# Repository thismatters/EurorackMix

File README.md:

# Mix

Audio signal mixing. Basic module with simple OP Amp design.

The KiCAD project here uses the library/footprints [found in my companion repo](https://github.com/thismatters/EurorackKiCAD).

## Size

30hp on a 1u rack.

## Inputs

4x patch inputs and 4x potentiometers for adjusting the apparent effect of a patch input

## Outputs

Single 1/4" phone jack output.
4 LED array indicating output level.

## Notes

LED array takes some cues from the [MFOS Multifunction Module](https://musicfromouterspace.com/analogsynth_new/MULTIFUNCTIONMODULE/pdf/mfm_schempg1_schem.pdf)

## Vendors

There are part numbers in the [BOM](mix.csv) for many of the parts (not for basic passives though) at the following vendors:

* [Mouser](https://www.mouser.com): Needs no introduction. Get your ICs from here (or [digikey](https://www.digikey.com)).
* [Tayda Electronics](https://www.taydaelectronics.com/): Good supplier for passive components; audio jacks, and potentiometers. Their audio jacks are slightly smaller than the thonkiconn from thonk.
* [Love My Switches](https://lovemyswitches.com/): Has [really good knobs](https://lovemyswitches.com/anodized-aluminum-knob-the-lo-fi-1-4-smooth-shaft-12-5mm-od/) to go on those potentiometers!
* [OSHPark](https://oshpark.com/): Fast and (relatively) cheap PCB manufacturer. The [V0 circuit](https://oshpark.com/shared_projects/xlEAsl8K) works pretty well as a mix, but the output level indicator doesn't quite work right, there will be another version.

## Changelog

### V1
- [x] Adds full bridge rectifier to output level indicator
- [x] Adds capacitor and resistor to output level indicator
- [x] Removes capacitor from output op amp
- [x] Updates design langage

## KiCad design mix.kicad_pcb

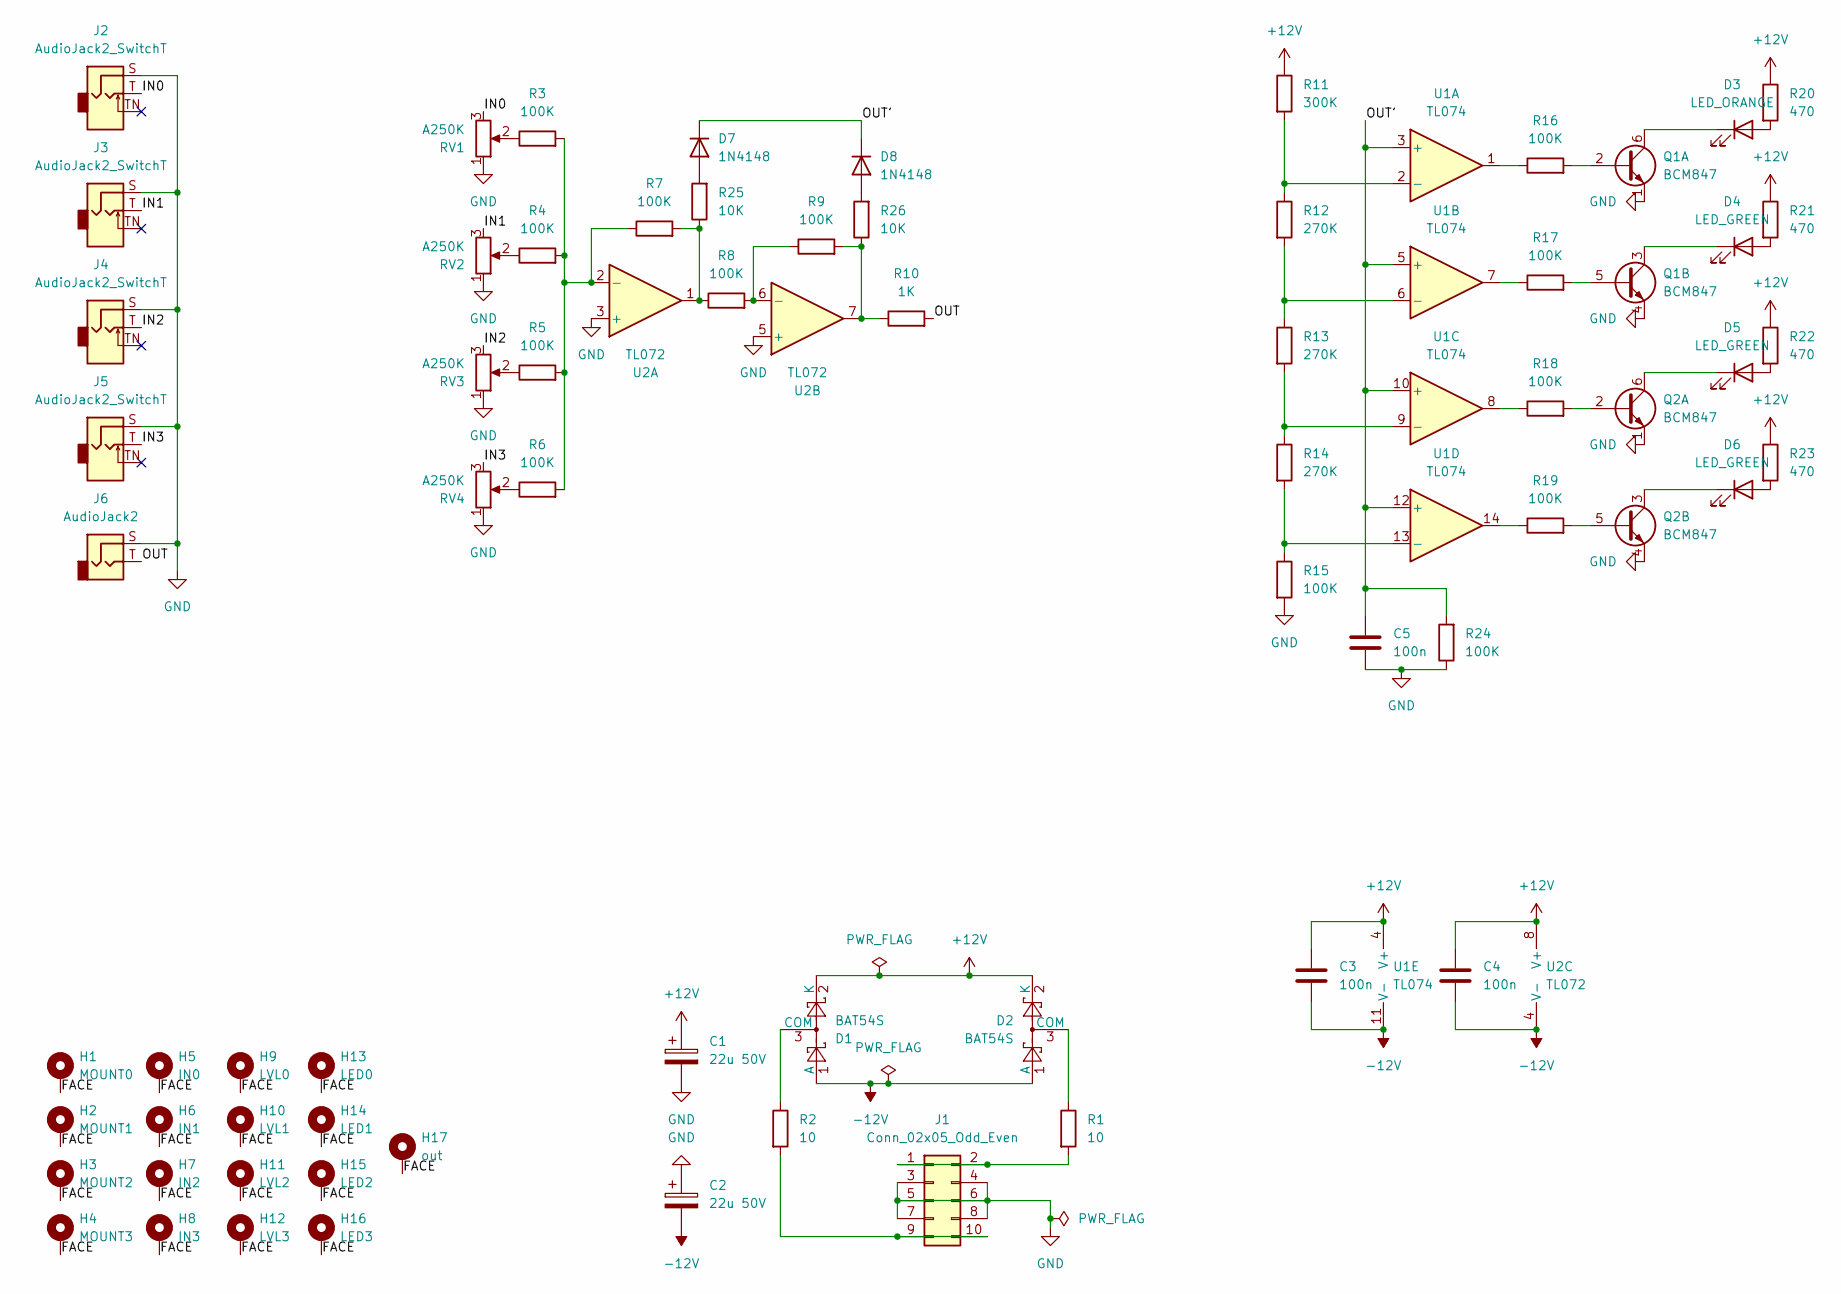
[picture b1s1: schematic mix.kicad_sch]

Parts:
C1, C2: 22u 50V; CP_Radial_D5.0mm_P2.50mm
C3, C4, C5: 100n; C_0805_2012Metric
D1, D2: BAT54S; SOT-23; PartNum 863-BAT54SLT1G
D3: LED_ORANGE; LED_D3.0mm
D4, D5, D6: LED_GREEN; LED_D3.0mm
D7, D8: 1N4148; D_SOD-323_HandSoldering
H1: MOUNT0; Mech-MountingHole
H2: MOUNT1; Mech-MountingHole
H3: MOUNT2; Mech-MountingHole
H4: MOUNT3; Mech-MountingHole
H5: IN0; Mech-AudioJack-Hole-Input
H6: IN1; Mech-AudioJack-Hole-Input
H7: IN2; Mech-AudioJack-Hole-Input
H8: IN3; Mech-AudioJack-Hole-Input
H9: LVL0; Mech-Potentiometer-Hole_level_90deg
H10: LVL1; Mech-Potentiometer-Hole_level_90deg
H11: LVL2; Mech-Potentiometer-Hole_level_90deg
H12: LVL3; Mech-Potentiometer-Hole_level_90deg
H13: LED0; Mech-LED-Hole-3mm-Bezel
H14: LED1; Mech-LED-Hole-3mm-Bezel
H15: LED2; Mech-LED-Hole-3mm-Bezel
H16: LED3; Mech-LED-Hole-3mm-Bezel
H17: out; Mech-Hole-10mm; PartNum 595-TL072CDR
J1: Conn_02x05_Odd_Even; PinHeader_2x05_P2.54mm_Vertical; PartNum A-2939
J2, J3, J4, J5: AudioJack2_SwitchT; AudioJack2_Tayda_A-2566; PartNum A-2566
J6: AudioJack2; AudioJack2_Tayda_A-1009; PartNum A-1009
Q1, Q2: BCM847; TSOP-6_1.65x3.05mm_P0.95mm; PartNum 771-BCM847DS135
R1, R2: 10; R_0805_2012Metric
R3, R4, R5, R6, R7, R8, R9, R15, R16, R17, R18, R19, R24: 100K; R_0805_2012Metric
R10: 1K; R_0805_2012Metric
R11: 300K; R_0805_2012Metric
R12, R13, R14: 270K; R_0805_2012Metric
R20, R21, R22, R23: 470; R_0805_2012Metric
R25, R26: 10K; R_0805_2012Metric
RV1, RV2, RV3, RV4: A250K; Potentiometer_RV16AF-41-15R1
U1: TL074; SOIC-14_3.9x8.7mm_P1.27mm; PartNum 595-TL074CDR
U2: TL072; SOIC-8_3.9x4.9mm_P1.27mm; PartNum 595-TL072CDR

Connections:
+12V: C1.1, C3.1, C4.1, D1.2 (K), D2.2 (K), R11.1, R20.1, R21.1, R22.1, R23.1, U1.4 (V+), U2.8 (V+)
-12V: C2.2, C3.2, C4.2, D1.1 (A), D2.1 (A), U1.11 (V-), U2.4 (V-)
/FACE: H1.1, H2.1, H3.1, H4.1, H5.1, H6.1, H7.1, H8.1, H9.1, H10.1, H11.1, H12.1, H13.1, H14.1, H15.1, H16.1, H17.1
/IN0: J2.T, RV1.3
/IN1: J3.T, RV2.3
/IN2: J4.T, RV3.3
/IN3: J5.T, RV4.3
/OUT: J6.T, R10.2
/OUT': C5.1, D7.1 (K), D8.1 (K), R24.2, U1.3 (+), U1.5 (+), U1.10 (+), U1.12 (+)
GND: C1.2, C2.1, C5.2, J1.3, J1.4, J1.5, J1.6, J1.7, J1.8, J2.S, J3.S, J4.S, J5.S, J6.S, Q1.1 (E1), Q1.4 (E2), Q2.1 (E1), Q2.4 (E2), R15.2, R24.1, RV1.1, RV2.1, RV3.1, RV4.1, U2.3 (+), U2.5 (+)
unnamed: D1.3 (COM), R2.1
unnamed: D2.3 (COM), R1.1
unnamed: D3.2 (A), R20.2
unnamed: D3.1 (K), Q1.6 (C1)
unnamed: D4.2 (A), R21.2
unnamed: D4.1 (K), Q1.3 (C2)
unnamed: D5.2 (A), R22.2
unnamed: D5.1 (K), Q2.6 (C1)
unnamed: D6.2 (A), R23.2
unnamed: D6.1 (K), Q2.3 (C2)
unnamed: D7.2 (A), R25.2
unnamed: D8.2 (A), R26.2
unnamed: J1.1, J1.2, R1.2
unnamed: J1.9, J1.10, R2.2
unnamed: Q1.2 (B1), R16.2
unnamed: Q1.5 (B2), R17.2
unnamed: Q2.2 (B1), R18.2
unnamed: Q2.5 (B2), R19.2
unnamed: R3.1, RV1.2
unnamed: R4.1, RV2.2
unnamed: R5.1, RV3.2
unnamed: R6.1, RV4.2
unnamed: R9.2, R10.1, R26.1, U2.7
unnamed: R16.1, U1.1
unnamed: R17.1, U1.7
unnamed: R18.1, U1.8
unnamed: R19.1, U1.14
unnamed: R7.2, R8.1, R25.1, U2.1
unnamed: R11.2, R12.1, U1.2 (-)
unnamed: R12.2, R13.1, U1.6 (-)
unnamed: R13.2, R14.1, U1.9 (-)
unnamed: R14.2, R15.1, U1.13 (-)
unnamed: R3.2, R4.2, R5.2, R6.2, R7.1, U2.2 (-)
unnamed: R8.2, R9.1, U2.6 (-)

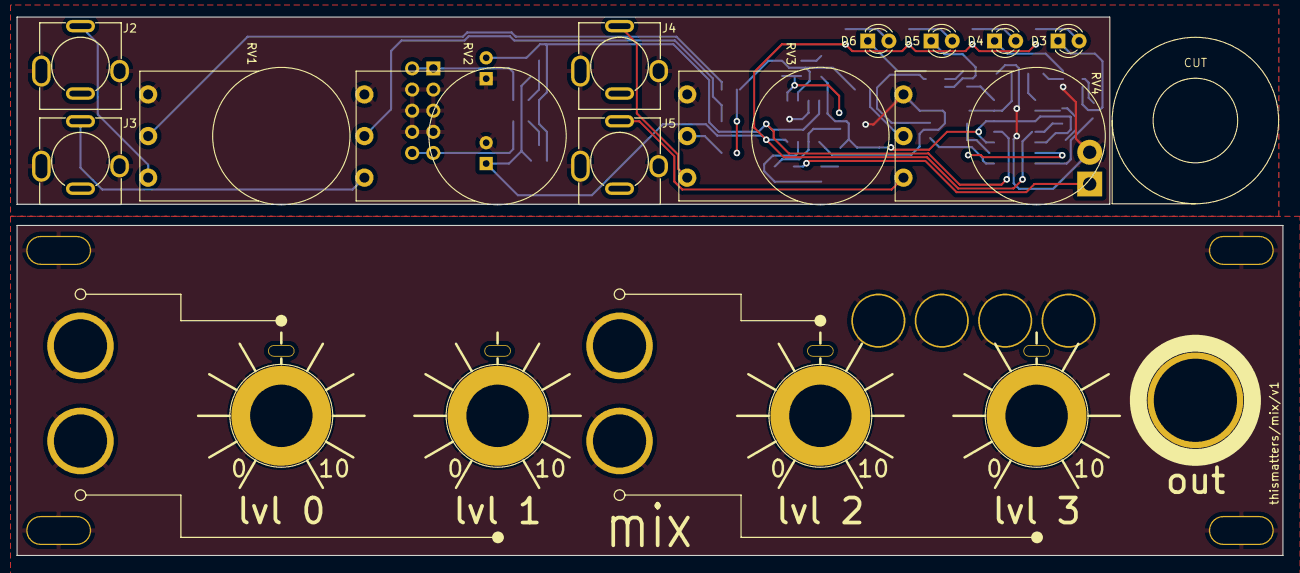
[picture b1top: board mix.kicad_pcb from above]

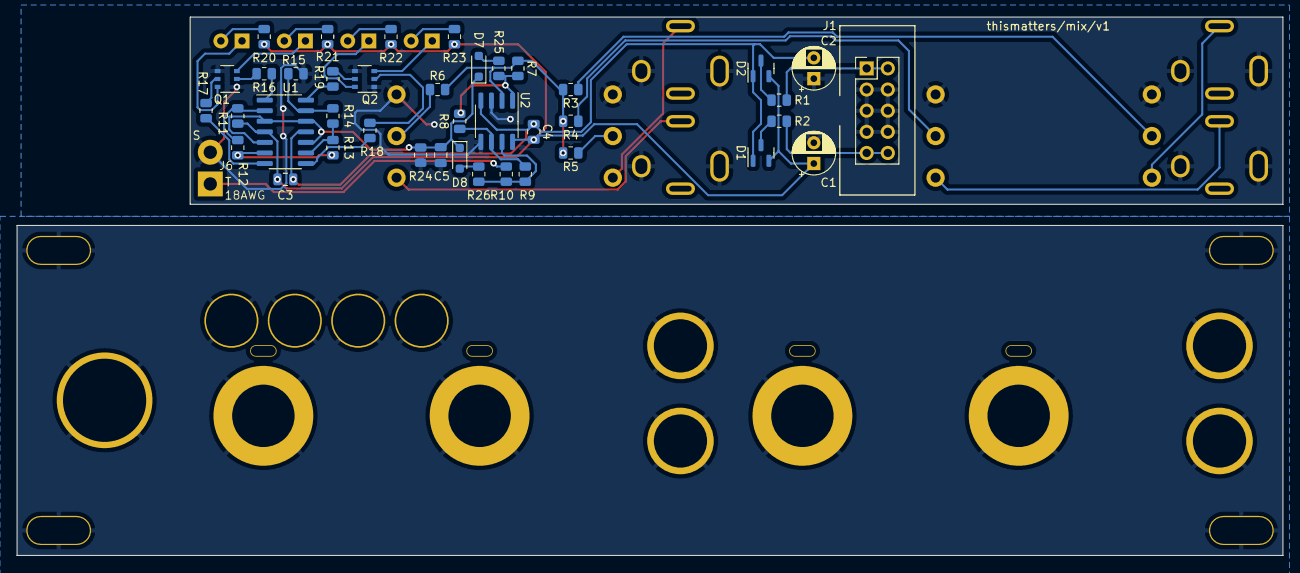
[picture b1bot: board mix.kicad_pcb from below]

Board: 2 copper layers, 152.1 x 64.7 mm, 70 parts (40 on the bottom side), 44 nets.

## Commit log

2024-07-13 pcb layed out
2024-07-13 Fixing BOM
2024-07-13 renaming project
2024-08-11 adding readme
2024-11-25 adding pcb to readme
